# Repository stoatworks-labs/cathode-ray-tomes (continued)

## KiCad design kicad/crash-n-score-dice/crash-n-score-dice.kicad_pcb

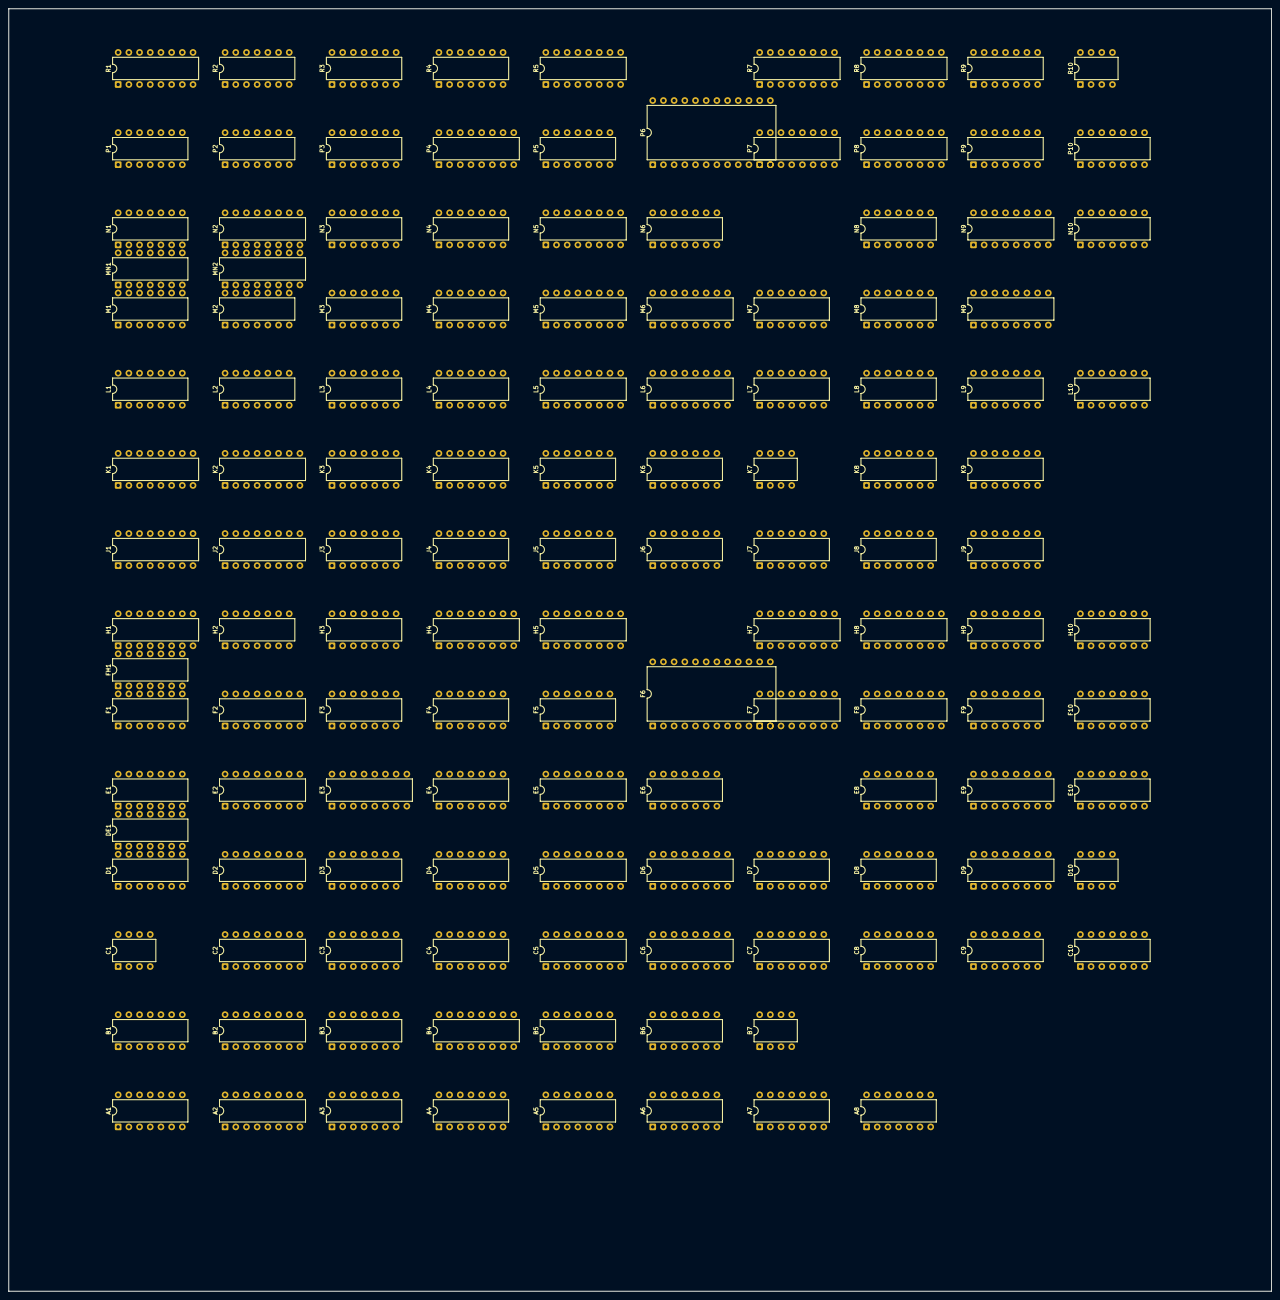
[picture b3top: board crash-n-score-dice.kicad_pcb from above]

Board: 2 copper layers, 300.0 x 304.7 mm, 132 parts (0 on the bottom side), 427 nets, no tracks yet.

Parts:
A1, A6: 7404; DIP-14_W7.62mm
A2: 9316; DIP-16_W7.62mm
A3: 7400; DIP-14_W7.62mm
A4: 7493; DIP-14_W7.62mm
A5, A7, A8: 7474; DIP-14_W7.62mm
B1: 7430; DIP-14_W7.62mm
B2: 9316; DIP-16_W7.62mm
B3: 7474; DIP-14_W7.62mm
B4: 7485; DIP-16_W7.62mm
B5: 7400; DIP-14_W7.62mm
B6: 7410; DIP-14_W7.62mm
B7: 555; DIP-8_W7.62mm
C1: 555; DIP-8_W7.62mm
C2, C5, C6: 9316; DIP-16_W7.62mm
C3, C10: 7404; DIP-14_W7.62mm
C4: 7420; DIP-14_W7.62mm
C7: 74107; DIP-14_W7.62mm
C8: 7402; DIP-14_W7.62mm
C9: 7400; DIP-14_W7.62mm
D1, D8: 7493; DIP-14_W7.62mm
D2: 74S287; DIP-16_W7.62mm
D3: 7410; DIP-14_W7.62mm
D4: 7486; DIP-14_W7.62mm
D5, D6: 9316; DIP-16_W7.62mm
D7: 7404; DIP-14_W7.62mm
D9: 7485; DIP-16_W7.62mm
D10: 555; DIP-8_W7.62mm
DE1: 7474; DIP-14_W7.62mm
E1: 7493; DIP-14_W7.62mm
E2: 74S287; DIP-16_W7.62mm
E3: 74192; DIP-16_W7.62mm
E4: 7400; DIP-14_W7.62mm
E5: 9316; DIP-16_W7.62mm
E6: 7402; DIP-14_W7.62mm
E8: 7420; DIP-14_W7.62mm
E9: 74193; DIP-16_W7.62mm
E10: 7404; DIP-14_W7.62mm
F1, F4: 7402; DIP-14_W7.62mm
F2: 74153; DIP-16_W7.62mm
F3: 7408; DIP-14_W7.62mm
F5: 74107; DIP-14_W7.62mm
F6: 82S115; DIP-24_W15.24mm
F7: 82S123; DIP-16_W7.62mm
F8: 74193; DIP-16_W7.62mm
F9: 7400; DIP-14_W7.62mm
F10: 7410; DIP-14_W7.62mm
FH1: 74107; DIP-14_W7.62mm
H1, H5: 9312; DIP-16_W7.62mm
H2: 7402; DIP-14_W7.62mm
H3: 7400; DIP-14_W7.62mm
H4: 9602; DIP-16_W7.62mm
H7: 7475; DIP-16_W7.62mm
H8: 74193; DIP-16_W7.62mm
H9: 7474; DIP-14_W7.62mm
H10: 7404; DIP-14_W7.62mm
J1: 7448; DIP-16_W7.62mm
J2: 9312; DIP-16_W7.62mm
J3, J6, J9: 7404; DIP-14_W7.62mm
J4: 7400; DIP-14_W7.62mm
J5, J7: 7474; DIP-14_W7.62mm
J8: 7408; DIP-14_W7.62mm
K1, K2: 74153; DIP-16_W7.62mm
K3, K4: 7474; DIP-14_W7.62mm
K5: 7400; DIP-14_W7.62mm
K6: 7410; DIP-14_W7.62mm
K7: 555; DIP-8_W7.62mm
K8: 7490; DIP-14_W7.62mm
K9: 7492; DIP-14_W7.62mm
L1, L2: 7490; DIP-14_W7.62mm
L3: 7486; DIP-14_W7.62mm
L4, L8: 7402; DIP-14_W7.62mm
L5, L6: 9316; DIP-16_W7.62mm
L7: 74107; DIP-14_W7.62mm
L9: 7400; DIP-14_W7.62mm
L10: 7406; DIP-14_W7.62mm
M1, M2: 7490; DIP-14_W7.62mm
M3: 7486; DIP-14_W7.62mm
M4: 7474; DIP-14_W7.62mm
M5, M6: 9316; DIP-16_W7.62mm
M7: 7404; DIP-14_W7.62mm
M8: 7493; DIP-14_W7.62mm
M9: 7485; DIP-16_W7.62mm
MN1: 7408; DIP-14_W7.62mm
MN2: 74279; DIP-16_W7.62mm
N1: 7474; DIP-14_W7.62mm
N2: 74279; DIP-16_W7.62mm
N3, N8: 7420; DIP-14_W7.62mm
N4, N6: 7402; DIP-14_W7.62mm
N5: 9316; DIP-16_W7.62mm
N9: 74193; DIP-16_W7.62mm
N10: 7404; DIP-14_W7.62mm
P1, P5: 74107; DIP-14_W7.62mm
P2: 7410; DIP-14_W7.62mm
P3, P9: 7400; DIP-14_W7.62mm
P4, P8: 74193; DIP-16_W7.62mm
P6: 82S115; DIP-24_W15.24mm
P7: 82S123; DIP-16_W7.62mm
P10: 7490; DIP-14_W7.62mm
R1: 9602; DIP-16_W7.62mm
R2, R9: 7474; DIP-14_W7.62mm
R3: 7404; DIP-14_W7.62mm
R4: 7432; DIP-14_W7.62mm
R5: 9312; DIP-16_W7.62mm
R7: 7475; DIP-16_W7.62mm
R8: 74193; DIP-16_W7.62mm
R10: 555; DIP-8_W7.62mm

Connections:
+5V: A1.14, A2.16, A3.14, A4.5, A5.14, A6.14, A7.14, A8.14, B1.14, B2.16, B3.14, B4.16, B5.14, B6.14, B7.8, C1.8, C2.16, C3.14, C4.14, C5.16, C6.16, C7.14, C8.14, C9.14, C10.14, D1.5, D3.14, D4.14, D5.16, D6.16, D7.14, D8.5, D9.16, D10.8, DE1.14, E1.5, E3.16, E4.14, E5.16, E6.14, E8.14, E9.16, E10.14, F1.14, F2.16, F3.14, F4.14, F5.14, F7.16, F8.16, F9.14, F10.14, FH1.14, H1.16, H2.14, H3.14, H5.16, H7.5, H8.16, H9.14, H10.14, J1.16, J2.16, J3.14, J4.14, J5.14, J6.14, J7.14, J8.14, J9.14, K1.16, K2.16, K3.14, K4.14, K5.14, K6.14, K7.8, K8.5, K9.5, L1.5, L2.5, L3.14, L4.14, L5.16, L6.16, L7.14, L8.14, L9.14, L10.14, M1.5, M2.5, M3.14, M4.14, M5.16, M6.16, M7.14, M8.5, M9.16, MN1.14, MN2.16, N1.14, N2.16, N3.14, N4.14, N5.16, N6.14, N8.14, N9.16, N10.14, P1.14, P2.14, P3.14, P4.16, P5.14, P7.16, P8.16, P9.14, P10.5, R2.14, R3.14, R4.14, R5.16, R7.5, R8.16, R9.14, R10.8
A2-15: A2.15, A3.9, B2.7, C2.7
A3-3: A3.3, P2.3
A3-6: A3.6, B3.10
A3-10: A3.10, B2.15
A3-11: A3.11, C3.1
A3-12: A3.12, B4.6, N4.11
A4-1: A4.1, A4.12, B4.13
A4-8: A4.8, B4.10
A4-9: A4.9, B4.15
A4-11: A4.11, B4.12
A4-14: A4.14, E4.8
A5-1: A5.1, B5.11
A5-5: A5.5, A5.12
A5-6: A5.6, B5.10
A6-4: A6.4, C6.2, D6.2
A6-12: A6.12, H9.2, H9.10
A7-4: A7.4, A7.10
A7-5: A7.5, A7.12
A7-8: A7.8, R2.2
B1-1: B1.1, D4.8
B1-8: B1.8, F1.2
B2-10: B2.10, C2.15
B3-2: B3.2, D3.12
B5-4: B5.4, B6.9, C5.15, F5.13
B5-5: B5.5, C5.7, D5.7, E5.15
B5-6: B5.6, C5.9, D5.9, E5.9
B6-3: B6.3, C6.7, D6.15
B6-4: B6.4, B6.11, C6.15
B6-5: B6.5, B6.10, F5.6
B6-12: B6.12, B7.2
C5-10: C5.10, D5.15
C6-11: C6.11, F5.9
C7-12: C7.12, C9.8
C7-13: C7.13, C8.1, C9.5
C8-2: C8.2, C8.13
C8-3: C8.3, C8.4
C8-5: C8.5, C9.10, E9.13
C9-1: C9.1, H10.13
C9-2: C9.2, E8.8, F10.1
C9-3: C9.3, E9.4
C9-9: C9.9, E9.12
C9-11: C9.11, D9.3
C10-6: C10.6, E4.12
D3-6: D3.6, J3.13
D3-8: D3.8, N4.8
D6-3: D6.3, D7.2
D6-4: D6.4, D7.4
D6-5: D6.5, D7.6
D6-6: D6.6, F7.4
D7-1: D7.1, F7.1
D7-3: D7.3, F7.2
D7-5: D7.5, F7.3
D7-8: D7.8, E5.5
D7-9: D7.9, E6.13
D7-12: D7.12, F7.15
DE1-8: DE1.8, E3.11
DE1-13: DE1.13, J3.6
E2-9: E2.9, F2.3
E2-10: E2.10, F2.4
E2-11: E2.11, F2.5
E2-12: E2.12, F2.6
E3-3: E3.3, F3.12
E3-4: E3.4, F3.6
E3-13: E3.13, F3.5, J3.5
E4-1: E4.1, E4.4, F3.10, F3.11
E4-11: E4.11, F3.13
E4-13: E4.13, J8.8
E5-3: E5.3, E6.4
E5-4: E5.4, E6.1
E5-6: E5.6, E6.10
E6-2: E6.2, F7.6
E6-5: E6.5, F7.5
E6-9: E6.9, F7.9
E6-12: E6.12, F7.7
E8-6: E8.6, F10.13
E9-5: E9.5, F10.12
F1-3: F1.3, F1.4
F2-7: F2.7, K3.12
F3-1: F3.1, J7.9
F3-3: F3.3, F4.6
F4-1: F4.1, F4.8, F4.12
F4-3: F4.3, F4.4, R3.13
F4-5: F4.5, J7.8, J7.12
F5-1: F5.1, H5.15
F5-4: F5.4, H5.14
F6-7: F6.7, H5.1
F6-8: F6.8, H5.2
F6-9: F6.9, H5.3
F6-10: F6.10, H5.4
F6-14: F6.14, H5.5
F6-15: F6.15, H5.6
F6-16: F6.16, H5.7
F6-17: F6.17, H5.9
F8-4: F8.4, F9.6
F8-5: F8.5, F9.3
F8-12: F8.12, H8.5
F8-13: F8.13, H8.4
F9-1: F9.1, F9.4, F9.11
F9-2: F9.2, H9.9
F9-5: F9.5, H9.8
F9-8: F9.8, F9.13
F9-12: F9.12, H9.6
F10-2: F10.2, H10.12
F10-3: F10.3, H10.10
F10-4: F10.4, N8.6
F10-5: F10.5, L9.2, N8.8
F10-6: F10.6, N9.5
GND: A1.7, A2.3, A2.4, A2.6, A2.8, A3.7, A4.2, A4.3, A4.10, A5.7, A6.7, A7.7, A8.7, B1.7, B2.3, B2.4, B2.8, B3.7, B4.2, B4.4, B4.8, B5.7, B6.7, B7.1, C1.1, C2.6, C2.8, C3.7, C4.7, C5.3, C5.4, C5.8, C6.3, C6.4, C6.5, C6.6, C6.8, C7.7, C8.7, C9.7, C10.7, D1.10, D2.13, D2.14, D3.7, D4.7, D5.6, D5.8, D6.8, D7.7, D8.2, D8.3, D8.10, D9.8, D10.1, DE1.7, E1.10, E2.13, E2.14, E3.8, E3.15, E4.7, E5.8, E6.7, E8.7, E9.1, E9.8, E9.9, E9.10, E9.15, E10.7, F1.7, F2.8, F3.7, F4.7, F5.7, F7.8, F8.1, F8.8, F8.9, F8.14, F9.7, F10.7, FH1.7, H1.3, H1.6, H1.8, H2.7, H3.7, H5.8, H7.12, H8.8, H8.10, H8.14, H8.15, H9.7, H10.7, J1.8, J2.1, J2.3, J2.5, J2.7, J2.8, J2.10, J3.7, J4.7, J5.7, J6.7, J7.7, J8.7, J9.7, K1.1, K1.8, K1.15, K2.1, K2.8, K2.15, K3.7, K4.7, K5.7, K6.7, K7.1, K8.10, K9.10, L1.6, L1.7, L1.10, L2.6, L2.7, L2.10, L3.7, L4.7, L5.3, L5.4, L5.8, L6.3, L6.4, L6.5, L6.6, L6.8, L7.7, L8.7, L9.7, L10.7, M1.6, M1.7, M1.10, M2.6, M2.7, M2.10, M3.7, M4.2, M4.7, M5.6, M5.8, M6.8, M7.7, M8.2, M8.3, M8.10, M9.8, MN1.7, MN2.8, N1.7, N2.8, N3.7, N4.7, N5.8, N6.7, N8.7, N9.1, N9.8, N9.9, N9.10, N9.15, N10.7, P1.4, P1.7, P1.11, P2.7, P3.7, P4.8, P5.7, P7.8, P8.1, P8.8, P8.9, P8.10, P8.14, P9.7, P10.10, R2.7, R3.7, R4.7, R5.8, R7.12, R8.8, R8.14, R8.15, R9.7, R10.1
H1-1: H1.1, H1.2, J1.13
H1-4: H1.4, H1.5, J1.14
H1-7: H1.7, H1.9, J1.10
H1-10: H1.10, H2.10
H1-15: H1.15, H2.11
H2-1: H2.1, H3.13
H2-2: H2.2, H3.2, J3.12
H2-3: H2.3, H3.5, J3.10
H2-6: H2.6, K3.5
H2-12: H2.12, J2.15
H2-13: H2.13, K3.2
H3-9: H3.9, K3.6
H4-5: H4.5, J4.6
H4-11: H4.11, J4.8
H9-3: H9.3, H9.12, H10.4
H9-11: H9.11, H10.6
H10-2: H10.2, R9.11
H10-8: H10.8, R9.3, R9.12
H10-11: H10.11, L9.1
J1-1: J1.1, K1.9
J1-2: J1.2, K2.7
J1-6: J1.6, K2.9
J1-7: J1.7, K1.7
J1-9: J1.9, J2.6
J1-11: J1.11, J2.9
J1-12: J1.12, J2.4
J1-15: J1.15, J2.2
J5-1: J5.1, K5.11
J5-5: J5.5, J5.12
J5-6: J5.6, K5.10
J6-4: J6.4, L6.2, M6.2
J6-12: J6.12, R9.2, R9.10
J7-1: J7.1, J8.6
J7-3: J7.3, J8.3
J7-11: J7.11, J8.11
J8-12: J8.12, L8.10
J9-2: J9.2, K4.2
J9-4: J9.4, K4.12
K1-3: K1.3, L2.1, L2.12, L3.5
K1-4: K1.4, L1.1, L1.12
K1-5: K1.5, M2.1, M2.12, M3.5
K1-6: K1.6, M1.1, M1.12
K1-10: K1.10, M1.9
K1-11: K1.11, M2.9, M3.12
K1-12: K1.12, L1.9
K1-13: K1.13, L2.9, L3.12
K2-3: K2.3, L2.8, L3.2
K2-4: K2.4, L1.8
K2-5: K2.5, M2.8, M3.2
K2-6: K2.6, M1.8
K2-10: K2.10, M1.11, M2.14
K2-11: K2.11, M2.11, M3.9
K2-12: K2.12, L1.11, L2.14
K2-13: K2.13, L2.11, L3.9
K4-1: K4.1, L4.1
K4-13: K4.13, L4.13
K5-4: K5.4, K6.9, L5.15, P5.13
K5-5: K5.5, L5.7, M5.7, N5.15
K5-6: K5.6, L5.9, M5.9, N5.9
K6-3: K6.3, L6.7, M6.15
K6-4: K6.4, K6.11, L6.15
K6-5: K6.5, K6.10, P5.6
K6-12: K6.12, K7.2
L3-1: L3.1, M3.1
L3-3: L3.3, N3.1, N3.13
L3-4: L3.4, M3.4
L3-6: L3.6, N3.4, N3.10
L3-8: L3.8, N3.5, N3.9
L3-10: L3.10, M3.10
L3-11: L3.11, N3.2, N3.12
L3-13: L3.13, M3.13
L4-3: L4.3, MN2.13
L4-10: L4.10, P2.4
L5-10: L5.10, M5.15
L6-11: L6.11, P5.9
L7-12: L7.12, L9.8
L7-13: L7.13, L8.1, L9.5
L8-2: L8.2, L8.13
L8-3: L8.3, L8.4
L8-5: L8.5, L9.10, N9.13
L9-3: L9.3, N9.4
L9-9: L9.9, N9.12
L9-11: L9.11, M9.3
M4-6: M4.6, N4.9
M6-3: M6.3, M7.2
M6-4: M6.4, M7.4
M6-5: M6.5, M7.6
M6-6: M6.6, P7.4
M7-1: M7.1, P7.1
M7-3: M7.3, P7.2
M7-5: M7.5, P7.3
M7-8: M7.8, N5.5
M7-9: M7.9, N6.13
M7-12: M7.12, P7.15
MN1-2: MN1.2, R4.11
MN1-3: MN1.3, P4.4
MN1-5: MN1.5, R1.10
N1-2: N1.2, N2.4, P1.12
N1-12: N1.12, N2.9, P1.9
N2-1: N2.1, N3.8
N2-10: N2.10, N3.6
N2-13: N2.13, P2.13
N2-15: N2.15, P2.1, R2.5
N4-1: N4.1, P4.5
N4-5: N4.5, R4.8
N4-6: N4.6, P4.7
N5-3: N5.3, N6.4
N5-4: N5.4, N6.1
N5-6: N5.6, N6.10
N6-2: N6.2, P7.6
N6-5: N6.5, P7.5
N6-9: N6.9, P7.9
N6-12: N6.12, P7.7
P1-2: P1.2, P3.5
P1-6: P1.6, P3.4
P2-12: P2.12, P3.9
P3-2: P3.2, R3.4
P3-11: P3.11, P4.14
P3-13: P3.13, P4.13
P4-2: P4.2, R4.10
P4-3: P4.3, R3.3
P4-6: P4.6, R4.9
P4-11: P4.11, P4.12
P5-1: P5.1, R5.15
P5-4: P5.4, R5.14
P6-7: P6.7, R5.1
P6-8: P6.8, R5.2
P6-9: P6.9, R5.3
P6-10: P6.10, R5.4
P6-14: P6.14, R5.5
P6-15: P6.15, R5.6
P6-16: P6.16, R5.7
P6-17: P6.17, R5.9
P8-4: P8.4, P9.6
P8-5: P8.5, P9.3
P8-12: P8.12, R8.5
P8-13: P8.13, R8.4
P9-1: P9.1, P9.4, P9.11
P9-2: P9.2, R9.9
P9-5: P9.5, R9.8
P9-8: P9.8, P9.13
P9-12: P9.12, R9.6
P10-1: P10.1, P10.12
P10-14: P10.14, R10.3
VCC: A2.1, A2.5, A2.7, A2.10, A5.2, A5.4, A5.10, A5.13, A7.1, A7.13, B1.11, B2.1, B2.5, B2.6, B3.1, B3.4, B3.13, B4.3, C2.1, C2.3, C2.4, C2.5, C2.10, C5.5, C5.6, C6.10, C7.1, C7.4, C7.8, C7.10, C7.11, D5.3, D5.4, D5.5, D5.10, D6.7, D6.10, D9.2, D9.4, D10.4, DE1.10, DE1.12, E5.7, E5.10, E9.11, F5.8, F5.11, F8.10, F8.15, FH1.1, FH1.4, H8.1, H8.9, H9.4, H9.13, J1.3, J1.5, J5.2, J5.4, J5.10, J5.13, J7.4, J7.10, K3.1, K3.10, K4.4, K4.10, L1.3, L2.3, L5.5, L5.6, L7.1, L7.4, L7.8, L7.10, L7.11, M1.3, M2.3, M4.1, M4.11, M4.12, M5.3, M5.4, M5.5, M5.10, M6.7, M6.10, M9.2, M9.4, N1.1, N1.13, N5.7, N5.10, N9.11, P3.10, P4.1, P4.9, P4.10, P4.15, P5.8, P5.11, P8.15, R1.11, R1.13, R2.1, R2.4, R8.1, R8.9, R8.10, R9.4, R9.13
_1CRSTARTn: K4.8, K5.1, M4.10, MN1.1
_1FI: C10.5, D8.1, D8.12, D9.1, E8.13
_1FII: M8.1, M8.12, M9.1, N8.13
_1H: A2.14, J3.1
_1Hn: J3.2, K3.3, K3.11
_1OR2CREDIT: P3.3, R3.5
_1OR2CREDITn: B5.2, L4.12, R3.6
_1V: E1.1, E1.12, E2.6
_2CREDITn: MN2.14, N4.4, P3.1, R3.1
_2CRSTARTn: K4.6, K5.2, M4.13, R4.13
_2FI: D8.9, D9.14, E8.10, F3.4
_2FII: M8.9, M9.14, N8.10
_2PLAYER: F1.6, L6.10, M4.8
_2V: D3.2, E1.9, E2.7, H1.11
_4FI: D8.8, D9.11, E8.9
_4FII: M8.8, M9.11, N8.9
_4H: A2.12, F2.14
_4V: D3.1, E1.8, E2.4, F1.8, H1.12, MN1.4
_8FI: A3.1, C7.9, D8.11, D9.9, F10.11
_8FII: L7.9, M8.11, M9.9
_8H: A2.11, F2.2, H2.8, J2.11
_8V: A1.5, D1.14, E1.11, F3.9, H1.13, J2.13, K3.13
_8Vn: A1.6, R4.12
_16FIIn: L7.6, L9.12
_16FIn: C7.6, C9.12
_16H: C2.14, C4.9, E2.5, H2.9, J2.12
_16V: B1.3, D1.1, D1.12, D2.3, N2.14, R2.3
_32H: C2.13, D2.5, J3.3
_32Hn: J3.4, K1.14, K2.14
_32V: B1.5, D1.9, D2.2, J8.1
_64H: A3.5, C2.12, C3.9, D2.6, F1.5
_64Hn: C3.8, D3.9, D4.10
_64V: A7.3, A7.11, B1.6, B4.14, C3.5, D1.8, D2.1, K4.3, K4.11
_128CVI: D8.14, F5.5
_128CVII: M8.14, P5.5
_128H: B1.2, B4.9, C2.11, C3.11, D2.7
_128Hn: C3.10, D3.10
_128V: A1.9, B4.1, D1.11, D2.15, FH1.12, MN2.15
_128Vn: A1.8, B1.4
_256H: A3.4, B2.14, B3.11, B4.11, C3.3, D2.4, D4.9, K1.2, K2.2
_256Hn: C3.4, D3.11, H2.5, H3.10
_256V: D3.13, FH1.3, M4.3
_256Vn: C4.10, FH1.2
_512H: B2.13, B3.3, B3.12, C3.13, E1.14
_512Hn: B1.12, C3.12, F2.1
_ATTRACT: J6.13, J7.6, J8.2, L10.5, L10.9
_ATTRACTI: A6.13, C10.12
_ATTRACTn: C10.13, E3.5, J7.5, L4.2, L4.11, L8.8, P1.1, P1.8
_BARRIERVIDEO: P2.5, R3.12
_BARRIORSn: F3.2, H3.11
_BBFI: B5.12, F4.13
_BBFII: F4.10, K5.12
_BG1n: N1.5, N2.2
_BG2n: N1.9, N2.11
_BLACKFLAGS: F4.2, N4.13, R3.11
_BLACKFLAGSn: C4.4, R3.10
_BLACKSCOREn: C4.2, H3.8
_BONUSCOIN: N4.2, P3.6, R1.12
_C0I: E5.14, H5.11
_C0II: N5.14, R5.11
_C1I: E5.13, H5.12
_C1II: N5.13, R5.12
_C2I: E5.12, H5.13
_C2II: N5.12, R5.13
_C3I: E5.11, F6.18
_C3II: N5.11, P6.18
_C4I: D5.14, F6.21
_C4II: M5.14, P6.21
_CARI: B5.13, B6.2, F5.3, J4.4, L4.9
_CARII: J4.10, K5.13, K6.2, P5.3
_CARIIPLUSSLICKS: B6.13, J4.3
_CARIIn: C4.1, J4.1, P5.2
_CARIPLUSSLICKS: J4.11, K6.13
_CARIn: F5.2, J4.13
_CARRESET2: J6.1, N4.10
_CARRESETI: A6.1, M4.5
_CARRESETIIn: J6.2, L5.1, L6.1, M5.1, M6.1, P5.10, P8.11, R8.11
_CARRESETIn: A6.2, C5.1, C6.1, D5.1, D6.1, E5.1, F5.10, F8.11, H8.11, N5.1
_CARWINDOWIIn: K6.8, R5.10
_CARWINDOWIn: B6.8, H5.10
_CLOCK: A1.2, A1.3, A2.2, B2.2, C2.2
_CLOCKI: A6.8, C5.2, D5.2, E5.2, F5.12
_CLOCKII: J6.8, L5.2, M5.2, N5.2, P5.12
_CLOCKn: A1.4, A6.9, J6.9
_COIN: N4.3, P3.8
_CRASHIIn: K5.8, L8.11, L8.12
_CRASHIn: B5.8, C8.11, C8.12
_CRASHSEQIIn: J5.9, K5.9, K6.1, K7.4
_CRASHSEQIn: A5.9, B5.9, B6.1, B7.4
_D1I: F7.11, H7.16
_D1II: P7.11, R7.16
_D2I: F7.12, H7.15
_D2II: P7.12, R7.15
_D3I: F7.13, H7.10
_D3II: P7.13, R7.10
_D4I: F7.14, H7.9
_D4II: P7.14, R7.9
_ENDGAME: B5.1, N1.3, N1.11, N10.11, P10.11
_ENDGAMEn: J8.4, N2.3, N2.12, N10.10, R10.4
_FC: C1.3, E4.9
_FLAGS: A3.13, J3.8
_FLAGSn: H3.6, J3.9, N4.12
_FLASHn: F10.8, J1.4
_GOI: D7.13, D9.5
_GOII: M7.13, M9.5
_GT1: F10.9, J8.9, P10.9
_GT2: F10.10, J8.10, P10.8
_HIT: C1.2, C1.4, D4.6, DE1.11
_HIT1: E4.2, F4.11, H4.4, H4.6
_HIT1n: D4.4, H4.7, H4.13
_HIT2: E4.5, F4.9, H4.10, H4.12
_HIT2n: D4.5, H4.3, H4.9
_HRESETn: A2.9, A3.8, B2.9, C2.9, P1.10, P1.13
_HSYNC: B3.8, C4.12
_L0I: D6.13, F6.22
_L0II: M6.13, P6.22
_L1I: D6.12, F6.23
_L1II: M6.12, P6.23
_L2I: D6.11, F6.1
_L2II: M6.11, P6.1
_MFI: D10.3, E4.10
_OBJ0: D2.12, E2.3, E3.1
_OBJ1: D2.11, D3.3, E2.2, E3.10
_OBJ2: D2.10, D3.4, E2.1, E3.9
_OBJ3: D2.9, D3.5, E2.15, J3.11
_Q: E10.10, J7.13, J8.5, N1.4, N1.10, P3.12
_Qn: E10.11, L8.9, P10.6, P10.7
_R0I: F6.2, F7.10, F8.6
_R0II: P6.2, P7.10, P8.6
_R1I: F6.3, F8.7, H7.2
_R1II: P6.3, P8.7, R7.2
_R2I: F6.4, H7.3, H8.3
_R2II: P6.4, R7.3, R8.3
_R3I: F6.5, H7.6, H8.2
_R3II: P6.5, R7.6, R8.2
_R4I: F6.6, H7.7, H8.6
_R4II: P6.6, R7.7, R8.6
_SA: E4.3, L1.14
_SB: E4.6, M1.14
_SCOREWINDOW: F1.1, K3.4
_SHAPES: H3.1, H3.4, H3.12, K3.9
_SKIDI: B7.3, D7.11, F9.10
_SKIDII: K7.3, M7.11, P9.10
_SKIDIIn: M7.10, R7.4, R7.13
_SKIDIn: D7.10, H7.4, H7.13
_SLICKSn: C4.5, H3.3, J4.2, J4.12
_SPEED1I: C9.13, E9.3
_SPEED1II: L9.13, N9.3
_SPEED2I: D9.10, E8.5, E9.2
_SPEED2II: M9.10, N8.5, N9.2
_SPEED3I: D9.12, E8.4, E9.6
_SPEED3II: M9.12, N8.4, N9.6
_SPEED4I: D9.13, E8.2, E9.7
_SPEED4II: M9.13, N8.2, N9.7
_SPEED5I: C7.3, C8.6, D9.15, E8.1
_SPEED5II: L7.3, L8.6, M9.15, N8.1
_START: C10.3, E3.14, J7.2, K5.3, L1.2, L2.2, M1.2, M2.2, P10.2, P10.3
_STARTn: C9.4, C10.4, L9.4, M4.4
_STOPI: C9.6, E9.14
_STOPII: L9.6, N9.14
_VCLOCKn: A6.3, C4.8, J6.3
_VRESET: A6.11, B3.6, D1.2, D1.3, E1.2, E1.3, F1.12, J6.11
_VRESETIIn: J5.3, J5.11, J6.10, N6.3, N6.6, N6.8, N6.11
_VRESETIn: A5.3, A5.11, A6.10, E6.3, E6.6, E6.8, E6.11
_VRESETn: B3.5, FH1.13
_VSYNC: F1.10, F1.11
_VSYNCn: C4.13, F1.9, F1.13
_VTCI: A6.6, E8.12, F9.9
_VTCII: J6.6, N8.12, P9.9
_VTCIIn: J6.5, K6.6, L6.9, M6.9, R9.1
_VTCIn: A6.5, B6.6, C6.9, D6.9, H9.1
_WHITEFLAG: A3.2, C3.2, J4.5, J4.9
_WHITESCORE: H2.4, L4.8

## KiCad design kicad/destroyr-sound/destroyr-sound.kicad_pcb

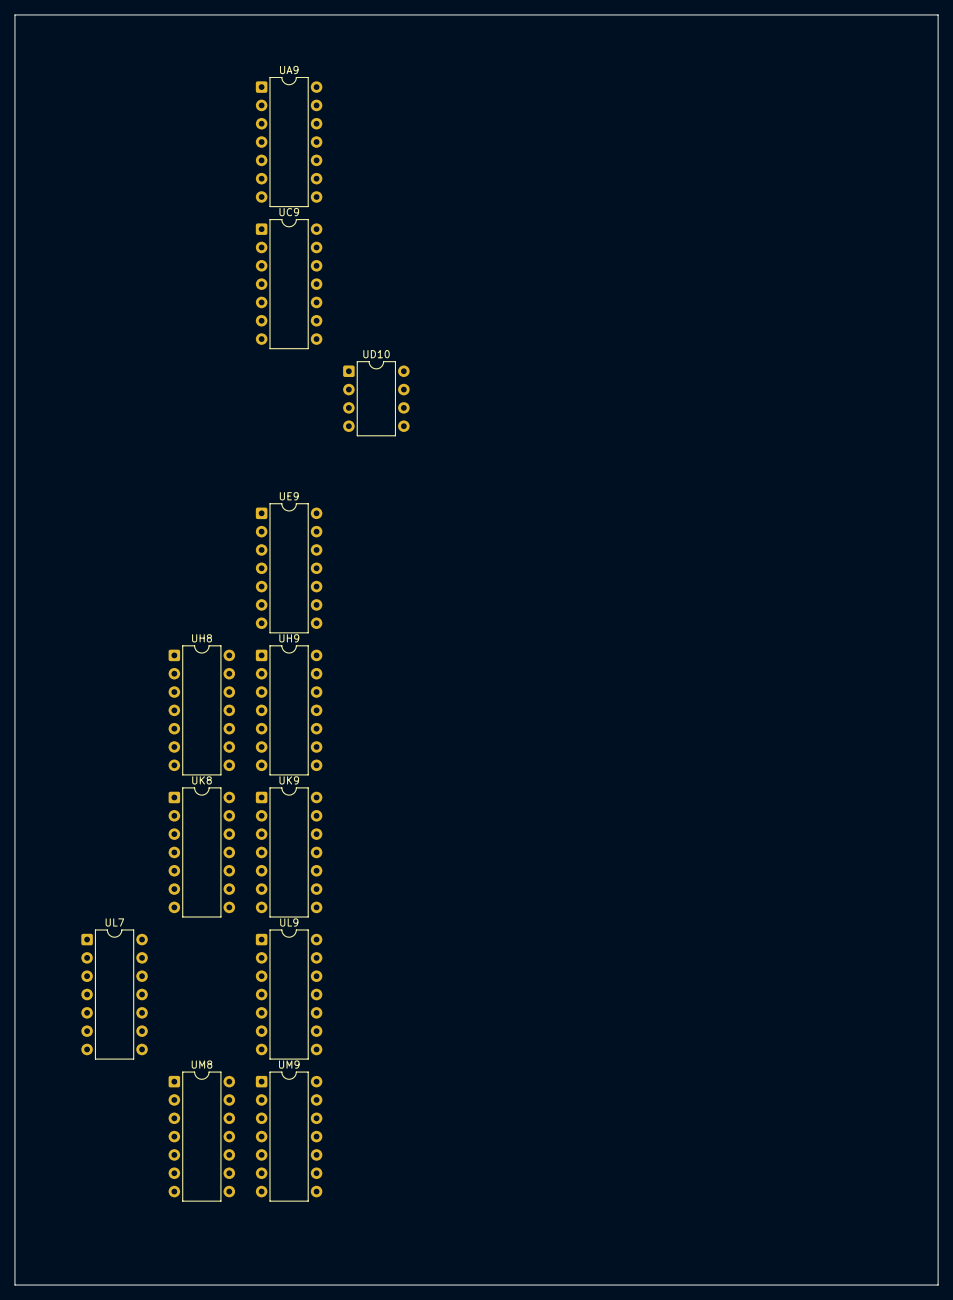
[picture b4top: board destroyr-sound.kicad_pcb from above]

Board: 2 copper layers, 128.0 x 176.1 mm, 12 parts (0 on the bottom side), 26 nets, no tracks yet.

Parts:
UA9: 7400; DIP-14_W7.62mm
UC9: LM324; DIP-14_W7.62mm
UD10: MC3340; DIP-8_W7.62mm
UE9: CD4066; DIP-14_W7.62mm
UH8: NE556; DIP-14_W7.62mm
UH9: LM324; DIP-14_W7.62mm
UK8: 7428; DIP-14_W7.62mm
UK9: 7404; DIP-14_W7.62mm
UL7: 7486; DIP-14_W7.62mm
UL9: 74LS164; DIP-14_W7.62mm
UM8: 7432; DIP-14_W7.62mm
UM9: 74LS164; DIP-14_W7.62mm

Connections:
+5V: UA9.14, UD10.8, UE9.14, UH8.14, UK8.14, UK9.14, UL7.14, UL9.14, UM8.14, UM9.14
+12V: UC9.4, UH9.4
-5V: UC9.11, UD10.3, UH9.11
EXPLO: UK8.3, UK8.8
GND: UA9.7, UC9.10, UE9.7, UH8.7, UK8.7, UK9.7, UL7.7, UL9.7, UM8.7, UM9.7
NOISE: UL9.9, UM9.9
NOISECLK: UL9.8, UM8.3, UM9.8
unnamed: UC9.5, UH8.2, UH8.6
unnamed: UC9.12, UH8.8, UH8.12
unnamed: UH9.3, UH9.5
unnamed: UC9.3, UH9.12
unnamed: UC9.6, UC9.7
unnamed: UH8.3, UH8.11
unnamed: UC9.13, UC9.14
unnamed: UK8.10, UK8.11
unnamed: UE9.3, UE9.11
unnamed: UC9.2, UE9.2
unnamed: UE9.5, UK8.13
unnamed: UK8.1, UM8.1
unnamed: UK8.4, UM8.2
unnamed: UK9.3, UM9.12
unnamed: UK9.4, UL7.13
unnamed: UL7.11, UL9.1, UL9.2
unnamed: UL9.13, UM9.1, UM9.2
RNOISE: UA9.4, UK8.12, UL7.12, UM9.11
SONLAT: UK8.6, UK8.9
